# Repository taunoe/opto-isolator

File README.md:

# Opto-isolator

The goal is to make isolated boards for external control of some equipment. To read signals and to send signals.

In my case it's a CO2 laser what I want automatically control.

_____
Tauno Erik 2024

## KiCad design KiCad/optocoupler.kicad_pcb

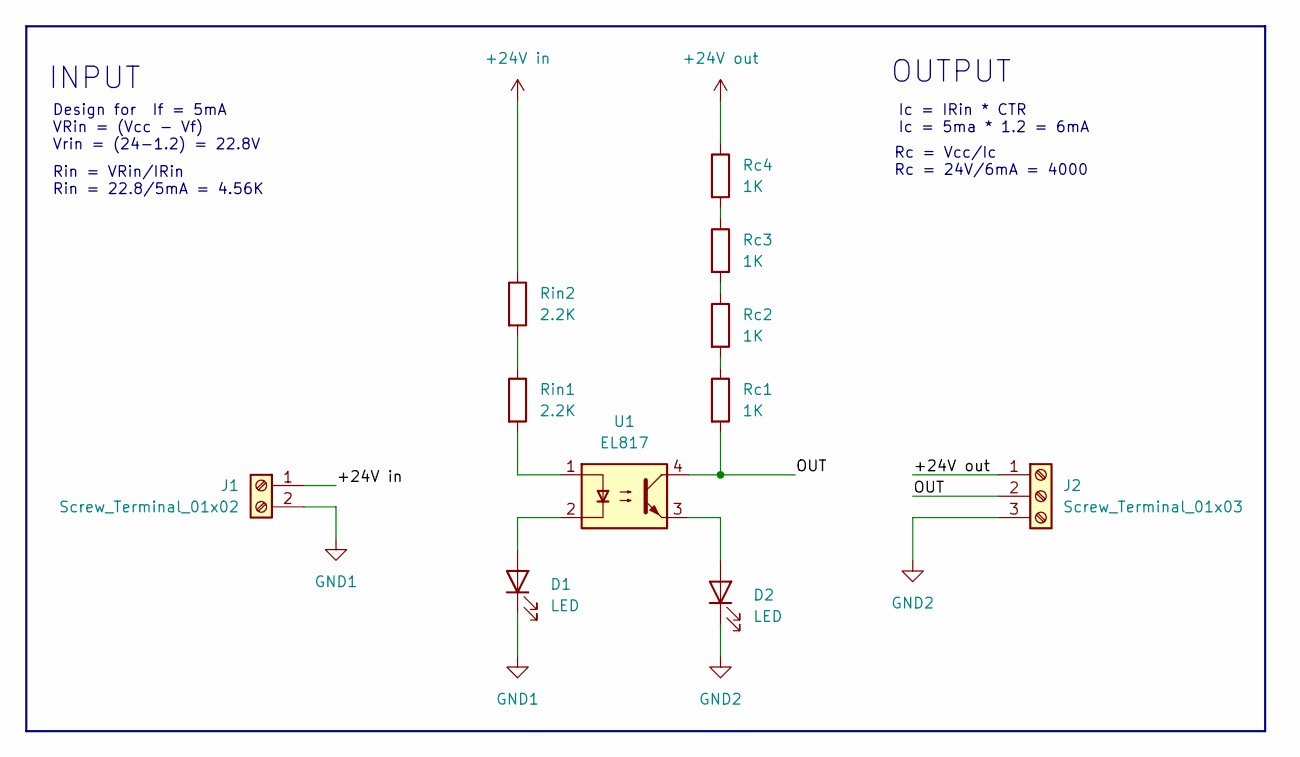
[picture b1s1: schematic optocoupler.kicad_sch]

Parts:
D1, D2: LED; LED_D5.0mm
J1: Screw_Terminal_01x02; TerminalBlock_bornier-2_P5.08mm
J2: Screw_Terminal_01x03; TerminalBlock_bornier-3_P5.08mm
Rc1, Rc2, Rc3, Rc4: 1K; R_Axial_DIN0204_L3.6mm_D1.6mm_P5.08mm_Horizontal
Rin1, Rin2: 2.2K; R_Axial_DIN0204_L3.6mm_D1.6mm_P5.08mm_Horizontal
U1: EL817; DIP-4_W7.62mm

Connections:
+24V in: J1.1, Rin2.1
+24V out: J2.1, Rc4.1
/OUT: J2.2, Rc1.2, U1.4; also elsewhere on the board
GND1: D1.1 (K), J1.2
GND2: D2.1 (K), J2.3
unnamed 5: D1.2 (A), U1.2; also elsewhere on the board
unnamed 6: D2.2 (A), U1.3; also elsewhere on the board
unnamed: Rc1.1, Rc2.2
unnamed: Rc2.1, Rc3.2
unnamed: Rc3.1, Rc4.2
unnamed: Rin1.1, Rin2.2
unnamed 11: Rin1.2, U1.1; also elsewhere on the board

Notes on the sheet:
Ic = IRin * CTR Ic = 5ma * 1.2 = 6mA
Design for If = 5mA VRin = (Vcc - Vf) Vrin = (24-1.2) = 22.8V
Rin = VRin/IRin Rin = 22.8/5mA = 4.56K
Rc = Vcc/Ic Rc = 24V/6mA = 4000
INPUT
OUTPUT

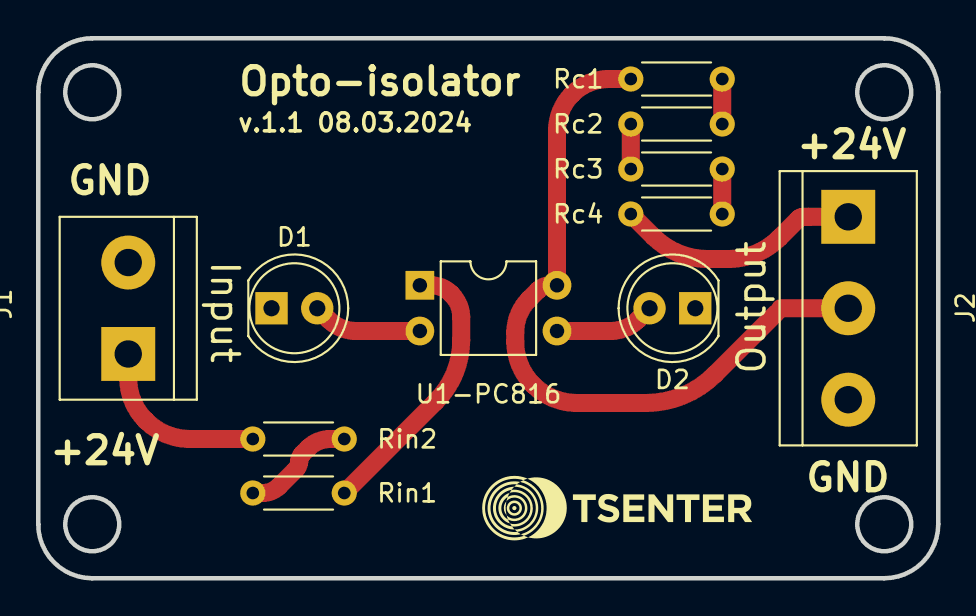
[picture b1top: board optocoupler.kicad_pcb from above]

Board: 2 copper layers, 50.0 x 30.0 mm, 11 parts (0 on the bottom side), 12 nets.

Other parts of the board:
U1-PC816: EL817; DIP-4_W7.62mm

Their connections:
/OUT: U1-PC816.4; also elsewhere on the board
unnamed 5: U1-PC816.2; also elsewhere on the board
unnamed 6: U1-PC816.3; also elsewhere on the board
unnamed 11: U1-PC816.1; also elsewhere on the board

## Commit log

2024-03-12 kicad files
2024-03-12 readme
2024-03-12 datasheets
2024-03-12 [ImgBot] Optimize images
    *Total -- 3,503.89kb -> 3,116.93kb (11.04%)
    /img/skeem.png -- 87.81kb -> 61.02kb (30.52%)
    /Screenshot 2024-03-07 150453.png -- 298.93kb -> 251.84kb (15.75%)
    /Laser_control_manual/IMG_20240312_085412.jpg -- 3,117.14kb -> 2,804.07kb (10.04%)
